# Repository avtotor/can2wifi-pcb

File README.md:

# can2wifi-pcb

Custom PCB for the [can2wifi](https://github.com/avtotor/can2wifi) firmware — a
**CAN → WiFi bridge** on ESP32-S3 that plugs into a vehicle OBD-II port, reads the
CAN bus via TWAI and streams frames over WiFi (Telnet :23, GVRET / SavvyCAN) and
UART. Targeted at **mass production via JLCPCB** (full PCBA).

> ⚠️ **Status: engineering draft — NOT yet fab-ready.** The schematic is complete
> and ERC-clean, footprints are assigned, components are placed and ground pours
> added. **Copper routing is NOT done** and several values need datasheet
> verification. See [Before you order](#before-you-order). Open the project in
> KiCad and finish/review it before sending anywhere.

## Design decisions

| Topic | Choice |
|---|---|
| Power | **12 V only** from OBD-II (pin 16) → DC-DC buck → 5 V → LDO → 3.3 V. USB is data-only. |
| Manufacturing | Full PCBA at JLCPCB (Gerber + BOM + CPL, LCSC parts). |
| Vehicle connector | **OBD-II J1962 male**, board-mounted, THT (hand-solder). |
| Protection | Extended: reverse-polarity, 12 V load-dump TVS, CAN common-mode choke + TVS, USB ESD. |
| CAN transceiver | **TJA1051T/3** (3.3 V VIO) instead of TJA1050 — removes the 1k/2k divider and the marginal 5 V TXD threshold. Firmware-compatible. |
| USB | CH340C USB-UART on UART0 (GPIO43/44) + dual-transistor auto-program. Native USB unavailable (GPIO20 used by CAN). |
| Board | 70 × 52 mm, 2-layer FR4 1.6 mm, GND pours both sides. |

## Architecture

```mermaid
flowchart TD
    OBD["OBD-II 12V"] --> F1["F1 PTC"] --> TVS["TVS SMBJ24A"] --> D2["D2 SS56 rev-pol"] --> V12["+12V"]
    V12 --> U4["U4 LM5164 buck 100V"] --> V5["+5V"]
    V5 --> U5["U5 AMS1117"] --> V3["+3V3"]
    V3 --> U1["U1 ESP32-S3"]
    USB["USB-C"] --> D4["D4 USBLC6 ESD"] -->|D+/D-| U3["U3 CH340C"]
    U3 -->|UART0| U1
    U3 -->|DTR/RTS| Q["Q1/Q2"] -->|EN / IO0| U1
    U1 -->|GPIO21/20| U2["U2 TJA1051"] --> L2["L2 CMC"] --> D3["D3 TVS"] --> CAN["CANH/CANL → OBD 6/14"]
```

## Signal map (from firmware)

| Net | ESP32-S3 pin | Notes |
|---|---|---|
| CAN_TX | IO21 | → TJA1051 TXD |
| CAN_RX | IO20 (module pin 14 "USB_D+") | ← TJA1051 RXD |
| LED_STAT | IO2 | active-high status LED (D7) |
| ESP_TX | TXD0 / IO43 | → CH340 RXD |
| ESP_RX | RXD0 / IO44 | ← CH340 TXD |
| EN | EN | RST button + RC + Q1 |
| IO0 | IO0 | BOOT button + Q2 |

> Native USB (GPIO19/20) is sacrificed: GPIO20 is the CAN RX pin, so programming
> goes through the CH340C on UART0. **On the bench, apply 12 V while flashing**
> (USB does not power the board). Optional DNP diode **D5** (VBUS→+5V) can be
> populated to power the board from USB for bench work.

## BOM (51 placements)

Assembly BOM with LCSC part numbers: [doc/can2wifi-pcb-bom-jlcpcb.csv](doc/can2wifi-pcb-bom-jlcpcb.csv)
(JLCPCB columns: Comment / Designator / Footprint / LCSC Part #). Plain BOM:
[doc/can2wifi-pcb-bom.csv](doc/can2wifi-pcb-bom.csv).

**44 of 51 placements have a verified in-stock LCSC number.** Still TBD (pick
before ordering): **D6/D7** LEDs (green/blue 0603), **F1** PPTC fuse (0.5 A 1812),
**R4** 31.6 k (set by buck feedback — verify), **R8** 120 Ω (DNP, not fitted),
**SW1/SW2** tactile buttons (match the PTS645 footprint), **J1** OBD-II connector
(hand-soldered, not JLCPCB-assembled).

| Ref | Value | Footprint |
|---|---|---|
| U1 | ESP32-S3-WROOM-1-N16R8 | RF_Module:ESP32-S3-WROOM-1 |
| U2 | TJA1051T/3 | SOIC-8 |
| U3 | CH340C | SOIC-16 |
| U4 | LM5164DDA (100 V sync buck) | SOIC-8-1EP ThermalVias |
| U5 | AMS1117-3.3 | SOT-223 |
| Q1, Q2 | MMBT3904 | SOT-23 |
| D1 | SMBJ24A (load-dump TVS) | SMB |
| D2 | SS34 (reverse-polarity, C115205) | SMA |
| D3 | PESD2CAN (CAN TVS) | SOT-23 |
| D4 | USBLC6-2SC6 (USB ESD) | SOT-23-6 |
| D5 | SS34 — **DNP** (USB→5V bench) | SMA |
| D6/D7 | Power / Status LED | 0603 |
| L1 | 33 µH (buck) | 12×12 mm |
| L2 | CAN common-mode choke | Coilcraft 1812CAN |
| F1 | PTC 0.5 A | 1812 |
| J1 | OBD-II J1962 male | can2wifi:OBD2_J1962_Male (custom) |
| J2 | USB-C 2.0 | HRO TYPE-C-31-M-12 |
| R1/R3 100k, R2 13k, R4 31.6k | LM5164 UVLO/RON/FB | 0603 |
| R5–R7 10k | EN/IO0 pull-ups | 0603 |
| R8 120Ω — **DNP** | CAN termination (bus already terminated) | 0805 |
| R9/R10 5.1k | USB-C CC | 0603 |
| R11/R12 1k | LED series | 0603 |
| R13 0Ω | CH340 V3↔3V3 link | 0603 |
| SW1/SW2 | RST / BOOT | PTS645 |
| C1–C17 | decoupling / bulk / buck | 0603/0805/1210 |

## Before you order

This board **must be finished and reviewed in KiCad** first. Checklist:

1. **Route the board.** No copper traces exist yet. Either install Java + the
   Freerouting JAR and run the MCP `autoroute`, or route manually in Pcbnew.
   Gerbers/CPL are only meaningful after routing.
2. **Clean up placement.** Auto-placement left courtyard overlaps (esp. around U1
   — the WROOM-1 footprint reserves a large keep-out/antenna area). Re-arrange so
   the ESP32 antenna sits over a board edge with copper keep-out beneath it.
3. **Verify the LM5164 buck values** against the TI datasheet / WEBENCH:
   `R3 (RON)` switching frequency, `L1` inductor, `R4/R5` feedback divider for
   5.0 V, `C4` feed-forward, input/output caps. These are reference-style
   placeholders, not silicon-verified.
4. **Verify the J1962 footprint** (`can2wifi.pretty/OBD2_J1962_Male`) against the
   exact OBD-II male connector you buy — pin pitch, row spacing and mounting holes
   are a generic 2×8 layout and will differ per part.
5. **Finish LCSC assignment** — 44/51 done; assign the 7 TBD lines (LEDs, fuse,
   buttons, R4 31.6k) and regenerate the BOM + CPL for assembly.
6. **Confirm the USB-C MPN** matches the `HRO TYPE-C-31-M-12` footprint.
7. Run **DRC** until clean, refill zones, then export Gerbers, drill, BOM and CPL.

## Files

| Path | Contents |
|---|---|
| `can2wifi-pcb.kicad_sch` | Schematic (ERC-clean: 0 errors) |
| `can2wifi-pcb.kicad_pcb` | Board: outline, placement, GND pours (unrouted) |
| `can2wifi.pretty/` | Custom J1962 footprint |
| `doc/can2wifi-pcb-schematic.pdf` | Schematic PDF |
| `doc/can2wifi-pcb-bom.csv` | BOM (grouped by value) |

## License

Proprietary — see [LICENSE](LICENSE).

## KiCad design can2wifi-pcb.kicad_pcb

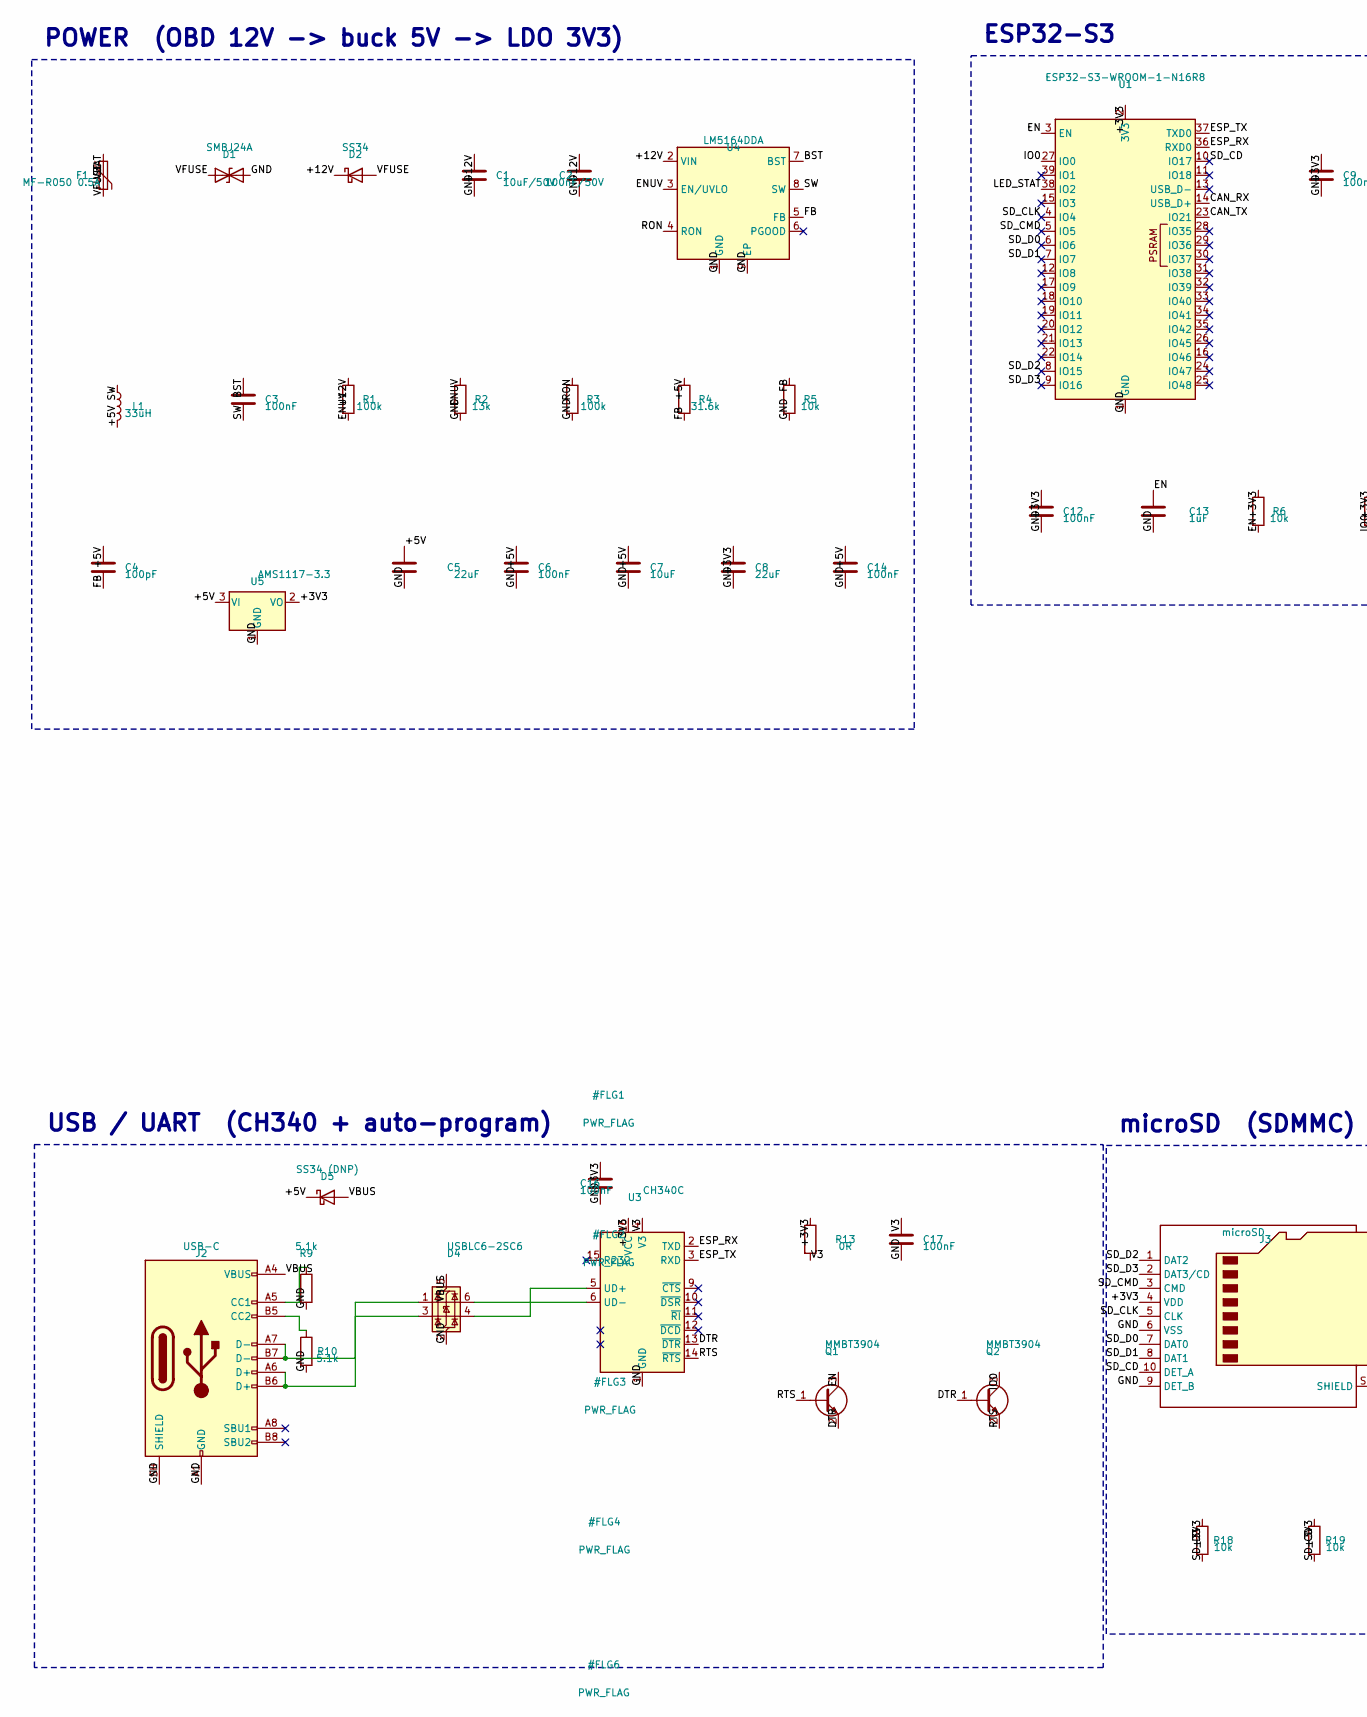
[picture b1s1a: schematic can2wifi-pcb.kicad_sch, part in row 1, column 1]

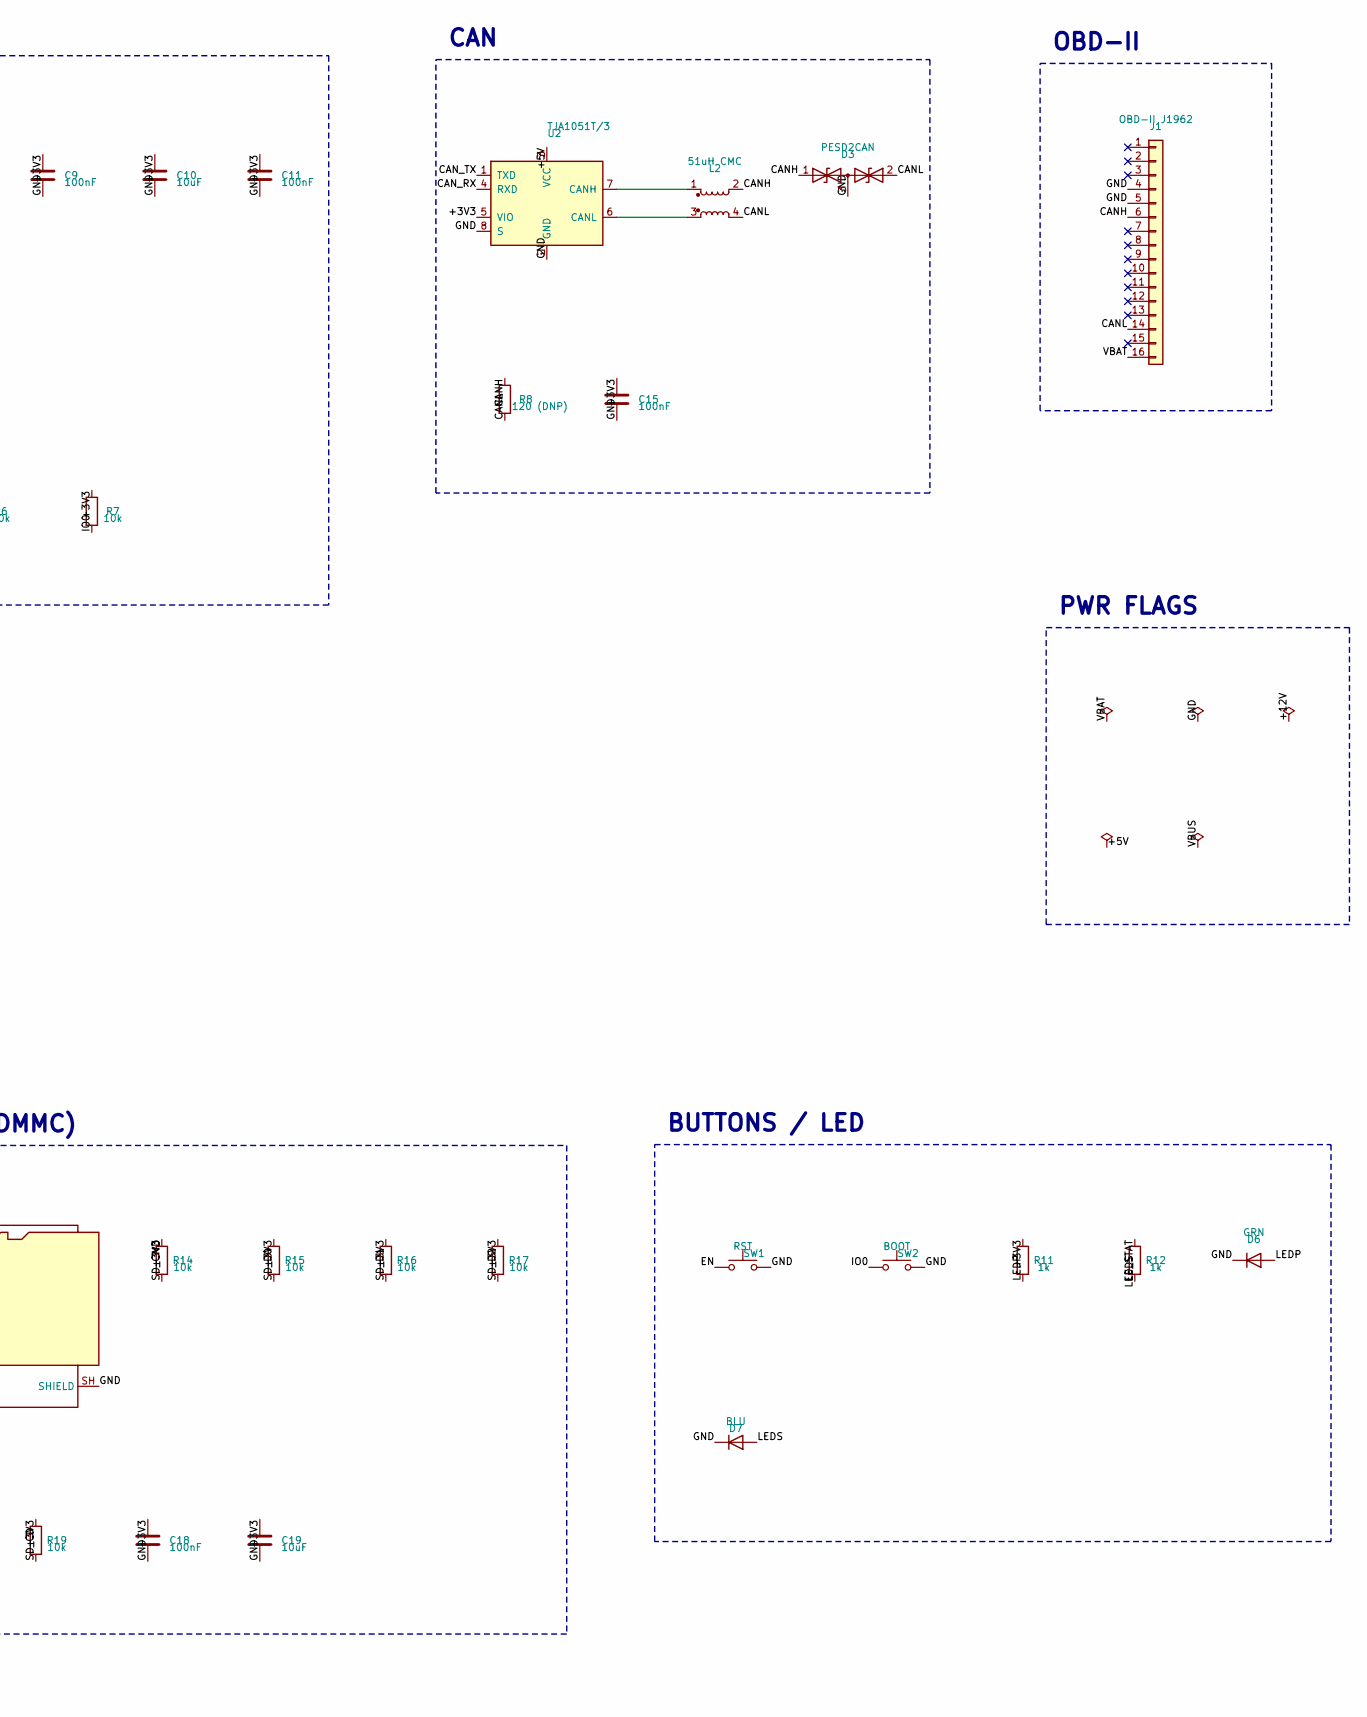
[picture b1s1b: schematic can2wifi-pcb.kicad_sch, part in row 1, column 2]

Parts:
C1: 10uF/50V; C_1210_3225Metric; LCSC C116808
C2: 100nF/50V; C_0603_1608Metric; LCSC C14663
C3, C6, C9, C11, C12, C14, C15, C16, C17: 100nF; C_0603_1608Metric; LCSC C14663
C4: 100pF; C_0603_1608Metric; LCSC C14858
C5, C8: 22uF; C_0805_2012Metric; LCSC C109314
C7, C10: 10uF; C_0805_2012Metric; LCSC C105505
C13: 1uF; C_0603_1608Metric; LCSC C105524
C18: 100nF; C_0603_1608Metric
C19: 10uF; C_0805_2012Metric
D1: SMBJ24A; D_SMB; LCSC C123819
D2: SS34; D_SMA; LCSC C115205
D3: PESD2CAN; SOT-23; LCSC C2687131
D4: USBLC6-2SC6; SOT-23-6; LCSC C19170930
D5: SS34 (DNP); D_SMA; LCSC C115205
D6: GRN; LED_0603_1608Metric
D7: BLU; LED_0603_1608Metric
F1: MF-R050 0.5A; R_1812_4532Metric
J1: OBD-II J1962; OBD2_J1962_Male
J2: USB-C; USB_C_Receptacle_HRO_TYPE-C-31-M-12; LCSC C165948
J3: microSD; microSD_HC_Hirose_DM3AT-SF-PEJM5
L1: 33uH; L_12x12mm_H8mm; LCSC C127788
L2: 51uH CMC; L_CommonModeChoke_Coilcraft_1812CAN; LCSC C49230370
Q1, Q2: MMBT3904; SOT-23; LCSC C111113
R1, R3: 100k; R_0603_1608Metric; LCSC C25803
R2: 13k; R_0603_1608Metric; LCSC C22797
R4: 31.6k; R_0603_1608Metric
R5, R6, R7: 10k; R_0603_1608Metric; LCSC C25804
R8: 120 (DNP); R_0805_2012Metric
R9, R10: 5.1k; R_0603_1608Metric; LCSC C23186
R11, R12: 1k; R_0603_1608Metric; LCSC C21190
R13: 0R; R_0603_1608Metric; LCSC C21189
R14, R15, R16, R17, R18, R19: 10k; R_0603_1608Metric
SW1: RST; SW_SPST_PTS645Sx43SMTR92
SW2: BOOT; SW_SPST_PTS645Sx43SMTR92
U1: ESP32-S3-WROOM-1-N16R8; ESP32-S3-WROOM-1; LCSC C2913202
U2: TJA1051T/3; SOIC-8_3.9x4.9mm_P1.27mm; LCSC C1850231
U3: CH340C; SOIC-16_3.9x9.9mm_P1.27mm; LCSC C84681
U4: LM5164DDA; SOIC-8-1EP_3.9x4.9mm_P1.27mm_EP2.41x3.3mm_ThermalVias; LCSC C477928
U5: AMS1117-3.3; SOT-223-3_TabPin2; LCSC C18164485

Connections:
+3V3: C8.1, C9.1, C10.1, C11.1, C12.1, C15.1, C16.1, C18.1, C19.1, J3.4 (VDD), R6.1, R7.1, R11.1, R13.1, R14.1, R15.1, R16.1, R17.1, R18.1, R19.1, U1.2 (3V3), U2.5 (VIO), U3.16 (VCC), U5.2 (VO)
+5V: C4.1, C5.1, C6.1, C7.1, C14.1, D5.1 (K), L1.2, R4.1, U2.3 (VCC), U5.3 (VI)
+12V: C1.1, C2.1, D2.1 (K), R1.1, U4.2 (VIN)
BST: C3.1, U4.7 (BST)
CANH: D3.1 (A1), J1.6, L2.2, R8.1
CANH_T: L2.1, U2.7 (CANH)
CANL: D3.2 (A2), J1.14, L2.4, R8.2
CANL_T: L2.3, U2.6 (CANL)
CAN_RX: U1.14 (USB_D+), U2.4 (RXD)
CAN_TX: U1.23 (IO21), U2.1 (TXD)
CC1: J2.A5 (CC1), R9.1
CC2: J2.B5 (CC2), R10.1
DTR: Q1.2 (E), Q2.1 (B), U3.13 (~DTR)
EN: C13.1, Q1.3 (C), R6.2, SW1.1, U1.3 (EN)
ENUV: R1.2, R2.1, U4.3 (EN/UVLO)
ESP_RX: U1.36 (RXD0), U3.2 (TXD)
ESP_TX: U1.37 (TXD0), U3.3 (RXD)
FB: C4.2, R4.2, R5.1, U4.5 (FB)
GND: C1.2, C2.2, C5.2, C6.2, C7.2, C8.2, C9.2, C10.2, C11.2, C12.2, C13.2, C14.2, C15.2, C16.2, C17.2, C18.2, C19.2, D1.2 (A2), D3.3 (common), D4.2 (GND), D6.1 (K), D7.1 (K), J1.4, J1.5, J2.A1 (GND), J2.A12 (GND), J2.B1 (GND), J2.B12 (GND), J2.SH (SHIELD), J3.6 (VSS), J3.9 (DET_B), J3.SH (SHIELD), R2.2, R3.2, R5.2, R9.2, R10.2, SW1.2, SW2.2, U1.1 (GND), U1.40 (GND), U1.41 (GND), U2.2 (GND), U2.8 (S), U3.1 (GND), U4.1 (GND), U4.9 (EP), U5.1 (GND)
IO0: Q2.3 (C), R7.2, SW2.1, U1.27 (IO0)
LEDP: D6.2 (A), R11.2
LEDS: D7.2 (A), R12.2
LED_STAT: R12.1, U1.38 (IO2)
RON: R3.1, U4.4 (RON)
RTS: Q1.1 (B), Q2.2 (E), U3.14 (~RTS)
SD_CD: J3.10 (DET_A), R19.2, U1.10 (IO17)
SD_CLK: J3.5 (CLK), U1.4 (IO4)
SD_CMD: J3.3 (CMD), R14.2, U1.5 (IO5)
SD_D0: J3.7 (DAT0), R15.2, U1.6 (IO6)
SD_D1: J3.8 (DAT1), R16.2, U1.7 (IO7)
SD_D2: J3.1 (DAT2), R17.2, U1.8 (IO15)
SD_D3: J3.2 (DAT3/CD), R18.2, U1.9 (IO16)
SW: C3.2, L1.1, U4.8 (SW)
USBC_DM: D4.3 (I/O2), J2.A7 (D-), J2.B7 (D-)
USBC_DP: D4.1 (I/O1), J2.A6 (D+), J2.B6 (D+)
V3: C17.1, R13.2, U3.4 (V3)
VBAT: F1.1, J1.16
VBUS: D4.5 (VBUS), D5.2 (A), J2.A4 (VBUS), J2.A9 (VBUS), J2.B4 (VBUS), J2.B9 (VBUS)
VFUSE: D1.1 (A1), D2.2 (A), F1.2

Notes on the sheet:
POWER (OBD 12V -> buck 5V -> LDO 3V3)
ESP32-S3
CAN
OBD-II
USB / UART (CH340 + auto-program)
microSD (SDMMC)
BUTTONS / LED
PWR FLAGS

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
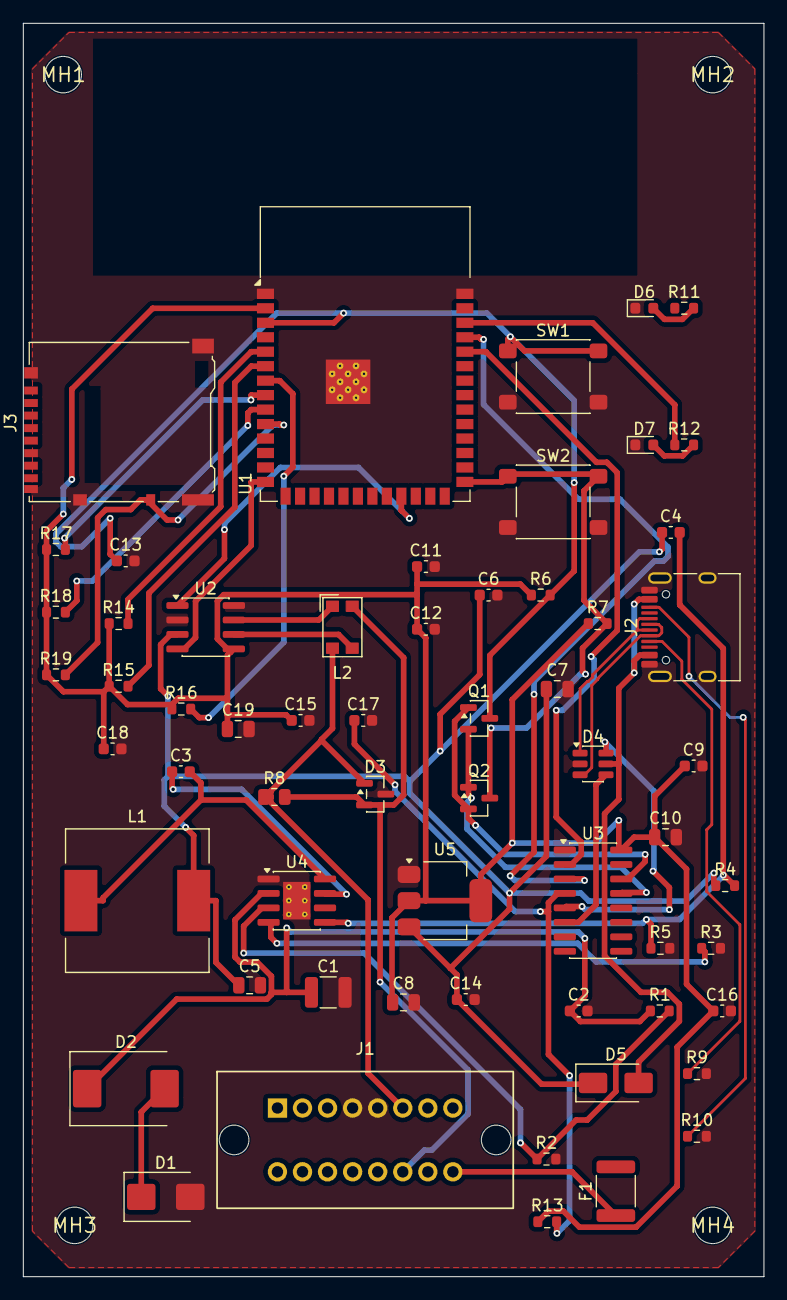
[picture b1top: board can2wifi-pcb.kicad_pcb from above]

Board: 2 copper layers, 65.0 x 110.0 mm, 64 parts (0 on the bottom side), 41 nets.

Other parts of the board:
MH1, MH2, MH3, MH4: MountingHole_3.2mm
